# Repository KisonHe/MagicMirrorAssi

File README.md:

# MagicMirrorAssi
Assist projects for the mirror

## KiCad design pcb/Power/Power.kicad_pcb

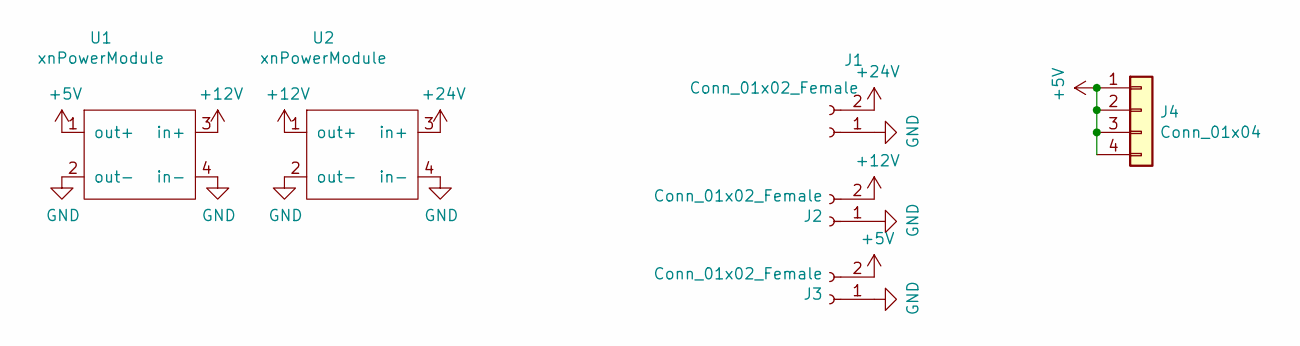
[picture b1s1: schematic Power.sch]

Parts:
J1, J2, J3: Conn_01x02_Female; AMASS_XT30U-M_1x02_P5.0mm_Vertical
J4: Conn_01x04; PinHeader_1x04_P2.54mm_Vertical
U1, U2: xnPowerModule

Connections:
+5V: J3.2, J4.1, J4.2, J4.3, J4.4, U1.1 (out+)
+12V: J2.2, U1.3 (in+), U2.1 (out+)
+24V: J1.2, U2.3 (in+)
GND: J1.1, J2.1, J3.1, U1.2 (out-), U1.4 (in-), U2.2 (out-), U2.4 (in-)

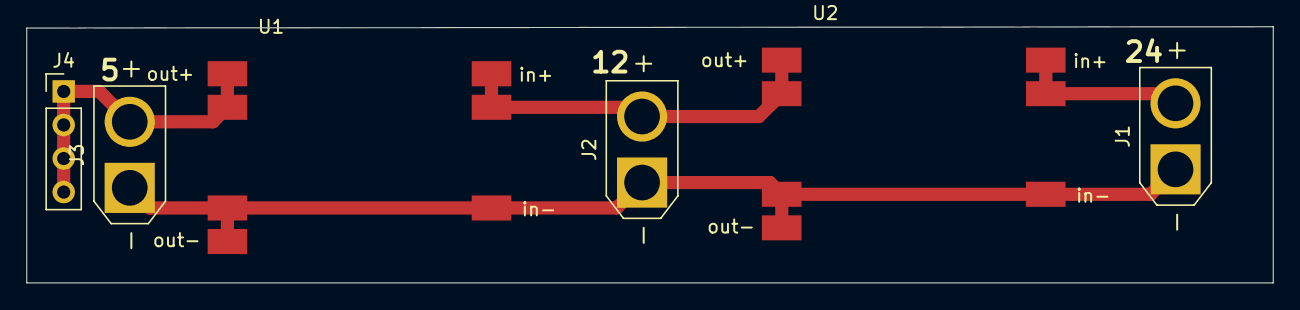
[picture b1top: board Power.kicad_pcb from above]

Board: 2 copper layers, 94.4 x 19.4 mm, 6 parts (0 on the bottom side), 4 nets.

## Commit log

2020-12-16 FrameWork
    Added Some frame as first Commit.
2020-12-16 KPE V1
2020-12-16 Fix README
2020-12-17 Modify KPE
2020-12-17 Modify SC
2020-12-17 Modify main
2020-12-20 Trace sdkconfig
2020-12-20 Prepare to abbandon KPE
    KPE is clearly not as nice as Closing Screen from Linux side:
    Though Screen Will complain for no sginal for a while,
    It is physically more stable
2020-12-20 rm old components. Trying git sub module
2021-02-10 Fix stuff
2021-02-13 Modify uart.py and bug fix 2 esp32 main
2021-02-14 Lots of things
2021-02-16 Moving to platform io
2021-03-11 Modify .ini
